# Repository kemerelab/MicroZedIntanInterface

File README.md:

# MicroZedIntanInterface

An FPGA data-acquisition interface for **Intan RHD2000-style neural recording chips**, built
on a **MicroZed** (Xilinx Zynq-7020) with a custom carrier PCB. The PL talks to up to two
cables of RHD2000 chips over a DDR SPI protocol; the PS streams the data over the network.

- Up to **256 channels @ 30 ksps** (two cables × 128 ch, Intan-standard 12-pin Omnetics, single + DDR).
- A user-programmable per-cable phase delay compensates for cable length.
- **TCP control** (port 0x6900 / 26880) + **UDP data stream** (port 0x6800 / 26624, ~9 MB/s per cable, ~18 MB/s at full config).
- Data path: `Intan ──SPI(DDR)──► PL ──BRAM──► (AXI CDMA) ──► PS ──UDP──► host`.

MicroZed SOMs are ~$300 (e.g. [Newark](https://www.newark.com/avnet/aes-z7mb-7z020-som-i-g-rev-h/eval-brd-32bit-fpga-arm-cortex/dp/62AJ7410)).
The [carrier PCB](pcb/KiCad-Project/) is manufactured at JLCPCB.

## Documentation

- **[Getting up and running](docs/getting-started.md)** — assembling the board (Omnetics
  epoxy), the MicroZed boot jumpers, copying the boot image to SD, and building from source.
- **[Command & packet structure](docs/protocol.md)** — the TCP command set, the UDP packet
  format, and the register map.
- **[CLAUDE.md](CLAUDE.md)** — architecture, build commands, and conventions for developers.
- **[ROADMAP.md](ROADMAP.md)** — status and planned work. **[overview.txt](overview.txt)** —
  the deeper architectural narrative.

## Host software

The board's protocol has two reference clients (both speak TCP control + UDP capture):

- **`remote/net.py`** — a single-file Python client for bring-up, cable/phase auto-detection,
  and testing. The human-readable reference for the command set and packet format.
- **[ephys-socket](https://github.com/ckemere/ephys-socket)** — the OpenEphys GUI plugin for
  real recording and visualization (neural + aux/accelerometer channels, fast settle, banked
  aux commands).

The firmware (`firmware/`), `remote/net.py`, and the plugin are the **three consumers of the
same register/packet contract** — keep them in sync when changing the protocol.

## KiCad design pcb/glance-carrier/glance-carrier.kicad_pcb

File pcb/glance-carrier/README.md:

# KiCad design files and production files

The PCB design was dervied from work by Viktor Nokolov licensed under the Creative Commons Zero license. His original project can be found here [https://github.com/viktor-nikolov/MicroZed-carrier-board](https://github.com/viktor-nikolov/MicroZed-carrier-board).

### Revision 1.0 Notes
Board revision 1.0 fixes the bug in 0.11, and transitions from 2 layer to 4 layer fabrication. This allows for
a smaller and slightly more case-friendly layout (digital IO on the same side of the PCB as Intan/Omnetics 
connectors, and USB-C power moved to the same side as the ethernet connector).

### Revision 0.11 Notes
Board revision 0.11 was used for initial testing. There was an error in the connectivity for the USB-UART
bridge. We fixed this with a bodge that is circled in the image below.

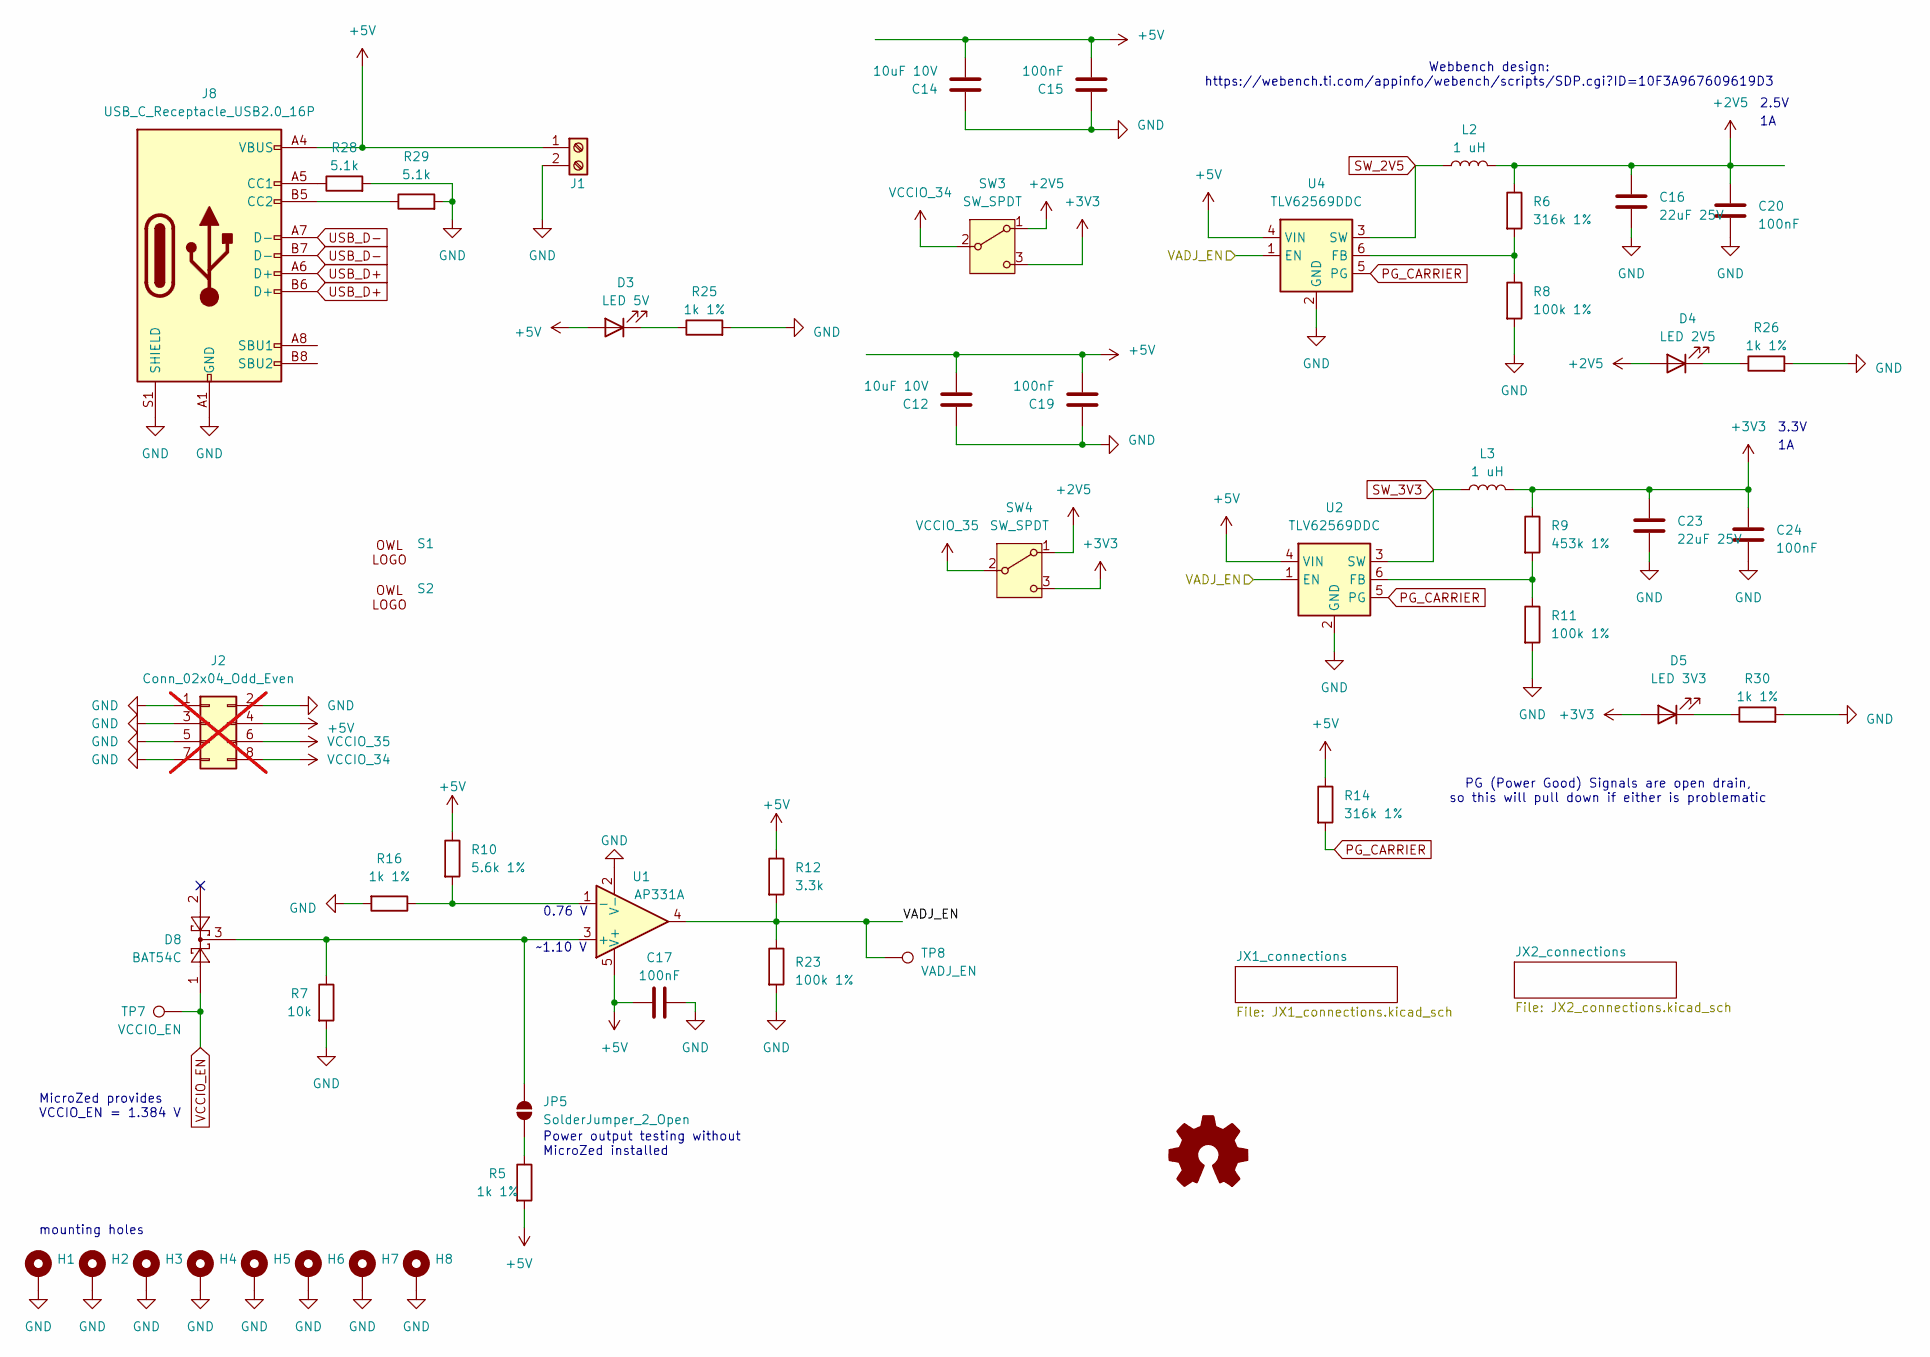
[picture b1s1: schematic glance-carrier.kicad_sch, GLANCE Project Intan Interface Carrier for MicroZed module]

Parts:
C12, C14: 10uF 10V; C_0603_1608Metric; LCSC C19702
C15, C17, C19, C20, C24: 100nF; C_0402_1005Metric; LCSC C307331
C16, C23: 22uF 25V; C_1206_3216Metric; LCSC C12891
D3: LED 5V; LED_0603_1608Metric; LCSC C2286
D4: LED 2V5; LED_0603_1608Metric; LCSC C2286
D5: LED 3V3; LED_0603_1608Metric; LCSC C2286
D8: BAT54C; SOT-23; LCSC C37704
H1, H2, H3, H4, H5, H6, H7, H8: MountingHole_3.2mm_M3_Pad
J1: Screw_Terminal_01x02; TerminalBlock_TE_282834-2_1x02_P2.54mm_Horizontal
J2: Conn_02x04_Odd_Even; PinSocket_2x04_P2.54mm_Vertical; not fitted
J8: USB_C_Receptacle_USB2.0_16P; USB_C_Receptacle_GCT_USB4105-xx-A_16P_TopMnt_Horizontal; LCSC C5184243
JP5: SolderJumper_2_Open; SolderJumper-2_P1.3mm_Open_RoundedPad1.0x1.5mm
L2, L3: 1 uH; L_1210_3225Metric; LCSC C47492669
R5, R16, R25, R26, R30: 1k 1%; R_0402_1005Metric; LCSC C11702
R6, R14: 316k 1%; R_0402_1005Metric; LCSC C4338094
R7: 10k; R_0402_1005Metric; LCSC C25744
R8, R11, R23: 100k 1%; R_0402_1005Metric; LCSC C25741
R9: 453k 1%; R_0402_1005Metric; LCSC C3025678
R10: 5.6k 1%; R_0402_1005Metric; LCSC C25908
R12: 3.3k; R_0402_1005Metric; LCSC C25890
R28, R29: 5.1k; R_0402_1005Metric; LCSC C25905
S1, S2: RICE_OWL_LOGO; not fitted
SW3, SW4: SW_SPDT; SW_SPDT_PCM12; LCSC C221841
TP7: VCCIO_EN; TestPoint_THTPad_D2.0mm_Drill1.0mm
TP8: VADJ_EN; TestPoint_THTPad_D2.0mm_Drill1.0mm
U1: AP331A; SOT-25-5_L3.0-W1.8-P0.95-LS3.0-BR; LCSC C151034
U2, U4: TLV62569DDC; SOT-23-6; LCSC C398365

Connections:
+2V5: C16.2, C20.1, D4.2 (A), L2.2, R6.1, SW3.1 (A), SW4.1 (A)
+3V3: C23.2, C24.1, D5.2 (A), L3.2, R9.1, SW3.3 (C), SW4.3 (C); also elsewhere on the board
+5V: C12.1, C14.1, C15.2, C17.1, C19.2, D3.2 (A), J1.1, J2.4, J8.A4 (VBUS), J8.A9 (VBUS), J8.B4 (VBUS), J8.B9 (VBUS), R5.2, R10.1, R12.1, R14.1, U1.5 (V+), U2.4 (VIN), U4.4 (VIN); also elsewhere on the board
/VADJ_EN: R12.2, R23.1, TP8.1, U1.4, U2.1 (EN), U4.1 (EN)
GND: C12.2, C14.2, C15.1, C16.1, C17.2, C19.1, C20.2, C23.1, C24.2, H1.1, H2.1, H3.1, H4.1, H5.1, H6.1, H7.1, H8.1, J1.2, J2.1, J2.2, J2.3, J2.5, J2.7, J8.A1 (GND), J8.A12 (GND), J8.B1 (GND), J8.B12 (GND), J8.S1 (SHIELD), R7.2, R8.2, R11.2, R16.2, R23.2, R25.2, R26.2, R28.2, R29.2, R30.2, U1.2 (V-), U2.2 (GND), U4.2 (GND); also elsewhere on the board
unnamed: D3.1 (K), R25.1
unnamed: D4.1 (K), R26.1
unnamed: D5.1 (K), R30.1
unnamed: J8.A5 (CC1), R28.1
unnamed: J8.B5 (CC2), R29.1
unnamed: D8.3, JP5.1 (A), R7.1, U1.3 (+)
unnamed: JP5.2 (B), R5.1
unnamed: R10.2, R16.1, U1.1 (-)
unnamed: R9.2, R11.1, U2.6 (FB)
unnamed: R6.2, R8.1, U4.6 (FB)
PG_CARRIER: R14.2, U2.5 (PG), U4.5 (PG); also elsewhere on the board
SW_2V5: L2.1, U4.3 (SW)
SW_3V3: L3.1, U2.3 (SW)
USB_D+: J8.A6 (D+), J8.B6 (D+); also elsewhere on the board
USB_D-: J8.A7 (D-), J8.B7 (D-); also elsewhere on the board
VCCIO_34: J2.8, SW3.2 (B); also elsewhere on the board
VCCIO_35: J2.6, SW4.2 (B); also elsewhere on the board
VCCIO_EN: D8.1, TP7.1; also elsewhere on the board

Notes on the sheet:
3.3V
mounting holes
2.5V
0.76 V
Webbench design: https://webench.ti.com/appinfo/webench/scripts/SDP.cgi?ID=10F3A967609619D3
~1.10 V
Power output testing without MicroZed installed
MicroZed provides VCCIO_EN = 1.384 V
PG (Power Good) Signals are open drain, so this will pull down if either is problematic

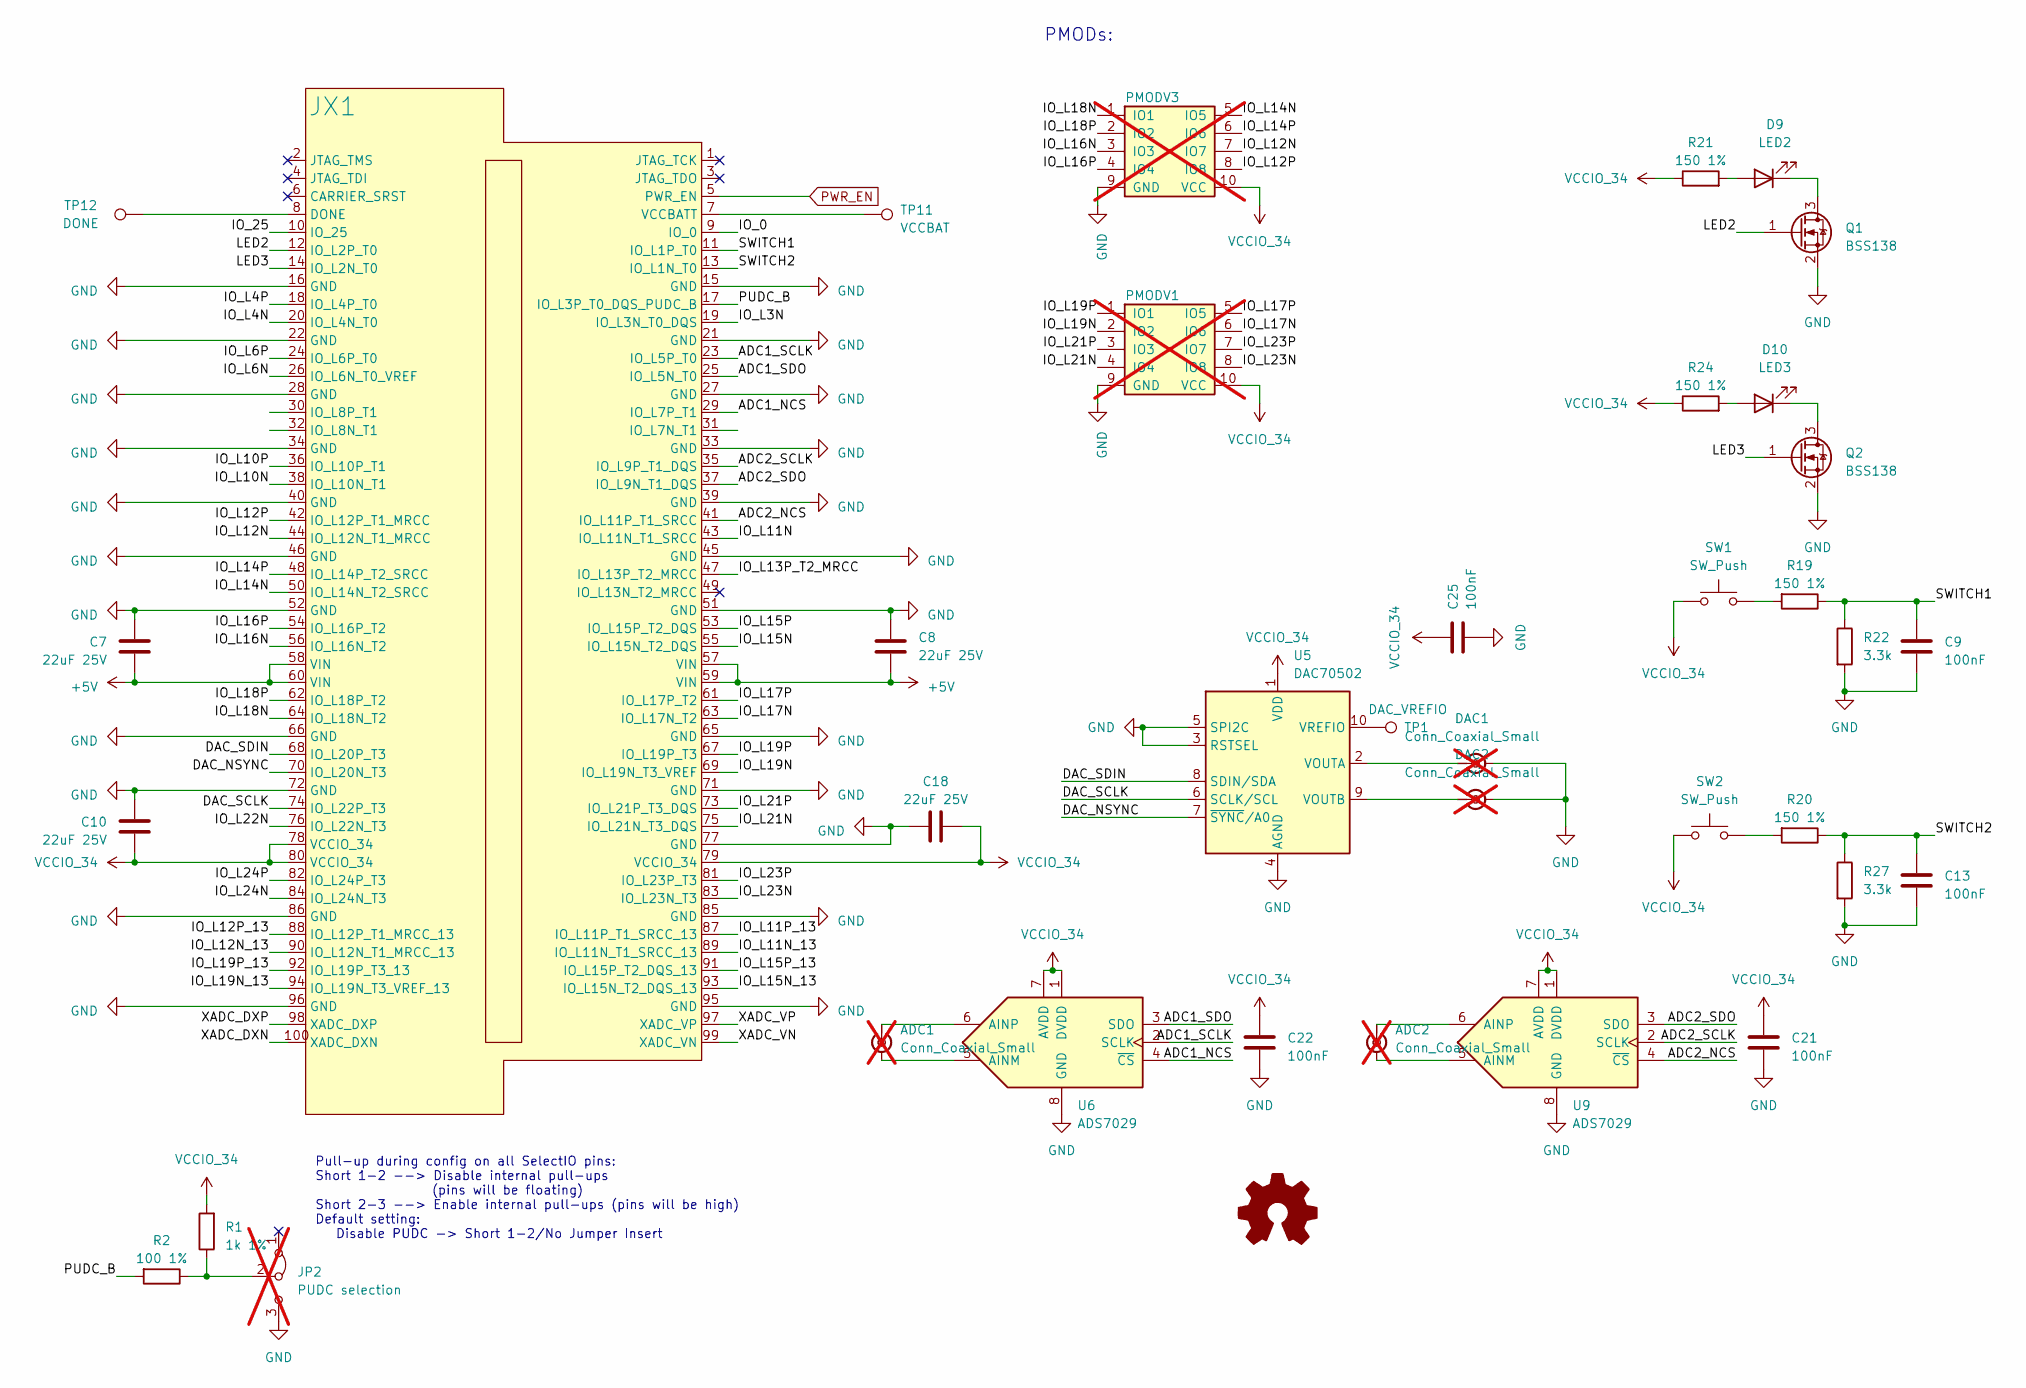
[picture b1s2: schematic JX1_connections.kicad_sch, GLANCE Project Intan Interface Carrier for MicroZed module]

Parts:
ADC1, ADC2: Conn_Coaxial_Small; SMA_Amphenol_901-143_Horizontal; not fitted
C7, C8, C10, C18: 22uF 25V; C_1206_3216Metric; LCSC C12891
C9, C13, C21, C22, C25: 100nF; C_0402_1005Metric; LCSC C307331
D9: LED2; LED_0603_1608Metric; LCSC C2286
D10: LED3; LED_0603_1608Metric; LCSC C2286
DAC1, DAC2: Conn_Coaxial_Small; SMA_Amphenol_901-143_Horizontal; not fitted
JP2: PUDC selection; PinHeader_1x03_P2.54mm_Vertical; not fitted
JX1: BergStak-100pos-plug-61083-101400; LCSC C2764776
PMODV1: PinSocket_2x06_P2.54mm_Vertical; not fitted
PMODV3: PMOD_Socket_Vertical; not fitted
Q1, Q2: BSS138; SOT-23; LCSC C400505
R1: 1k 1%; R_0402_1005Metric; LCSC C11702
R2: 100 1%; R_0402_1005Metric; LCSC C25076
R19, R20, R21, R24: 150 1%; R_0402_1005Metric; LCSC C25082
R22, R27: 3.3k; R_0402_1005Metric; LCSC C25890
SW1, SW2: SW_Push; SW_SPST_TS-1088-xR020; LCSC C720477
TP1: DAC_VREFIO; TestPoint_THTPad_D2.0mm_Drill1.0mm
TP11: VCCBAT; TestPoint_THTPad_D2.0mm_Drill1.0mm
TP12: DONE; TestPoint_THTPad_D2.0mm_Drill1.0mm
U5: DAC70502; Texas_DRX_WSON-10_2.5x2.5mm_P0.5mm; LCSC C880348
U6, U9: ADS7029; VSSOP-8_2.3x2mm_P0.5mm; LCSC C2669867

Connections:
+5V: C7.1, C8.1, JX1.57 (VIN), JX1.58 (VIN), JX1.59 (VIN), JX1.60 (VIN); also elsewhere on the board
/JX1_connections/ADC1_NCS: JX1.29 (IO_L7P_T1), U6.4 (~CS)
/JX1_connections/ADC1_SCLK: JX1.23 (IO_L5P_T0), U6.2 (SCLK)
/JX1_connections/ADC1_SDO: JX1.25 (IO_L5N_T0), U6.3 (SDO)
/JX1_connections/ADC2_NCS: JX1.41 (IO_L11P_T1_SRCC), U9.4 (~CS)
/JX1_connections/ADC2_SCLK: JX1.35 (IO_L9P_T1_DQS), U9.2 (SCLK)
/JX1_connections/ADC2_SDO: JX1.37 (IO_L9N_T1_DQS), U9.3 (SDO)
/JX1_connections/DAC_NSYNC: JX1.70 (IO_L20N_T3), U5.7 (~SYNC/A0)
/JX1_connections/DAC_SCLK: JX1.74 (IO_L22P_T3), U5.6 (SCLK/SCL)
/JX1_connections/DAC_SDIN: JX1.68 (IO_L20P_T3), U5.8 (SDIN/SDA)
/JX1_connections/IO_0: JX1.9 (IO_0)
/JX1_connections/IO_25: JX1.10 (IO_25)
/JX1_connections/IO_L3N: JX1.19 (IO_L3N_T0_DQS)
/JX1_connections/IO_L4N: JX1.20 (IO_L4N_T0)
/JX1_connections/IO_L4P: JX1.18 (IO_L4P_T0)
/JX1_connections/IO_L6N: JX1.26 (IO_L6N_T0_VREF)
/JX1_connections/IO_L6P: JX1.24 (IO_L6P_T0)
/JX1_connections/IO_L10N: JX1.38 (IO_L10N_T1)
/JX1_connections/IO_L10P: JX1.36 (IO_L10P_T1)
/JX1_connections/IO_L11N: JX1.43 (IO_L11N_T1_SRCC)
/JX1_connections/IO_L11N_13: JX1.89 (IO_L11N_T1_SRCC_13)
/JX1_connections/IO_L11P_13: JX1.87 (IO_L11P_T1_SRCC_13)
/JX1_connections/IO_L12N: JX1.44 (IO_L12N_T1_MRCC), PMODV3.7 (IO7)
/JX1_connections/IO_L12N_13: JX1.90 (IO_L12N_T1_MRCC_13)
/JX1_connections/IO_L12P: JX1.42 (IO_L12P_T1_MRCC), PMODV3.8 (IO8)
/JX1_connections/IO_L12P_13: JX1.88 (IO_L12P_T1_MRCC_13)
/JX1_connections/IO_L13P_T2_MRCC: JX1.47 (IO_L13P_T2_MRCC)
/JX1_connections/IO_L14N: JX1.50 (IO_L14N_T2_SRCC), PMODV3.5 (IO5)
/JX1_connections/IO_L14P: JX1.48 (IO_L14P_T2_SRCC), PMODV3.6 (IO6)
/JX1_connections/IO_L15N: JX1.55 (IO_L15N_T2_DQS)
/JX1_connections/IO_L15N_13: JX1.93 (IO_L15N_T2_DQS_13)
/JX1_connections/IO_L15P: JX1.53 (IO_L15P_T2_DQS)
/JX1_connections/IO_L15P_13: JX1.91 (IO_L15P_T2_DQS_13)
/JX1_connections/IO_L16N: JX1.56 (IO_L16N_T2), PMODV3.3 (IO3)
/JX1_connections/IO_L16P: JX1.54 (IO_L16P_T2), PMODV3.4 (IO4)
/JX1_connections/IO_L17N: JX1.63 (IO_L17N_T2), PMODV1.6 (IO6)
/JX1_connections/IO_L17P: JX1.61 (IO_L17P_T2), PMODV1.5 (IO5)
/JX1_connections/IO_L18N: JX1.64 (IO_L18N_T2), PMODV3.1 (IO1)
/JX1_connections/IO_L18P: JX1.62 (IO_L18P_T2), PMODV3.2 (IO2)
/JX1_connections/IO_L19N: JX1.69 (IO_L19N_T3_VREF), PMODV1.2 (IO2)
/JX1_connections/IO_L19N_13: JX1.94 (IO_L19N_T3_VREF_13)
/JX1_connections/IO_L19P: JX1.67 (IO_L19P_T3), PMODV1.1 (IO1)
/JX1_connections/IO_L19P_13: JX1.92 (IO_L19P_T3_13)
/JX1_connections/IO_L21N: JX1.75 (IO_L21N_T3_DQS), PMODV1.4 (IO4)
/JX1_connections/IO_L21P: JX1.73 (IO_L21P_T3_DQS), PMODV1.3 (IO3)
/JX1_connections/IO_L22N: JX1.76 (IO_L22N_T3)
/JX1_connections/IO_L23N: JX1.83 (IO_L23N_T3), PMODV1.8 (IO8)
/JX1_connections/IO_L23P: JX1.81 (IO_L23P_T3), PMODV1.7 (IO7)
/JX1_connections/IO_L24N: JX1.84 (IO_L24N_T3)
/JX1_connections/IO_L24P: JX1.82 (IO_L24P_T3)
/JX1_connections/LED2: JX1.12 (IO_L2P_T0), Q1.1 (G)
/JX1_connections/LED3: JX1.14 (IO_L2N_T0), Q2.1 (G)
/JX1_connections/PUDC_B: JX1.17 (IO_L3P_T0_DQS_PUDC_B), R2.2
/JX1_connections/SWITCH1: C9.1, JX1.11 (IO_L1P_T0), R19.1, R22.1
/JX1_connections/SWITCH2: C13.1, JX1.13 (IO_L1N_T0), R20.1, R27.1
/JX1_connections/XADC_DXN: JX1.100 (XADC_DXN)
/JX1_connections/XADC_DXP: JX1.98 (XADC_DXP)
/JX1_connections/XADC_VN: JX1.99 (XADC_VN)
/JX1_connections/XADC_VP: JX1.97 (XADC_VP)
GND: C7.2, C8.2, C9.2, C10.2, C13.2, C18.2, C21.2, C22.2, C25.2, DAC1.2 (Ext), DAC2.2 (Ext), JP2.3 (B), JX1.15 (GND), JX1.16 (GND), JX1.21 (GND), JX1.22 (GND), JX1.27 (GND), JX1.28 (GND), JX1.33 (GND), JX1.34 (GND), JX1.39 (GND), JX1.40 (GND), JX1.45 (GND), JX1.46 (GND), JX1.51 (GND), JX1.52 (GND), JX1.65 (GND), JX1.66 (GND), JX1.71 (GND), JX1.72 (GND), JX1.77 (GND), JX1.85 (GND), JX1.86 (GND), JX1.95 (GND), JX1.96 (GND), PMODV1.9 (GND), PMODV3.9 (GND), Q1.2 (S), Q2.2 (S), R22.2, R27.2, U5.3 (RSTSEL), U5.4 (AGND), U5.5 (SPI2C), U6.8 (GND), U9.8 (GND); also elsewhere on the board
unnamed: ADC1.2 (Ext), U6.5 (AINM)
unnamed: ADC1.1 (In), U6.6 (AINP)
unnamed: ADC2.2 (Ext), U9.5 (AINM)
unnamed: ADC2.1 (In), U9.6 (AINP)
unnamed: D9.2 (A), R21.2
unnamed: D9.1 (K), Q1.3 (D)
unnamed: D10.2 (A), R24.2
unnamed: D10.1 (K), Q2.3 (D)
unnamed: DAC1.1 (In), U5.2 (VOUTA)
unnamed: DAC2.1 (In), U5.9 (VOUTB)
unnamed: JP2.2 (C), R1.1, R2.1
unnamed: JX1.8 (DONE), TP12.1
unnamed: JX1.7 (VCCBATT), TP11.1
unnamed: R19.2, SW1.2
unnamed: R20.2, SW2.2
unnamed: TP1.1, U5.10 (VREFIO)
PWR_EN: JX1.5 (PWR_EN)
VCCIO_34: C10.1, C18.1, C21.1, C22.1, C25.1, JX1.78 (VCCIO_34), JX1.79 (VCCIO_34), JX1.80 (VCCIO_34), PMODV1.10 (VCC), PMODV3.10 (VCC), R1.2, R21.1, R24.1, SW1.1, SW2.1, U5.1 (VDD), U6.1 (DVDD), U6.7 (AVDD), U9.1 (DVDD), U9.7 (AVDD); also elsewhere on the board

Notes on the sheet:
PMODs:
Pull-up during config on all SelectIO pins: Short 1-2 --> Disable internal pull-ups (pins will be floating) Short 2-3 --> Enable internal pull-ups (pins will be high) Default setting: Disable PUDC -> Short 1-2/No Jumper Insert

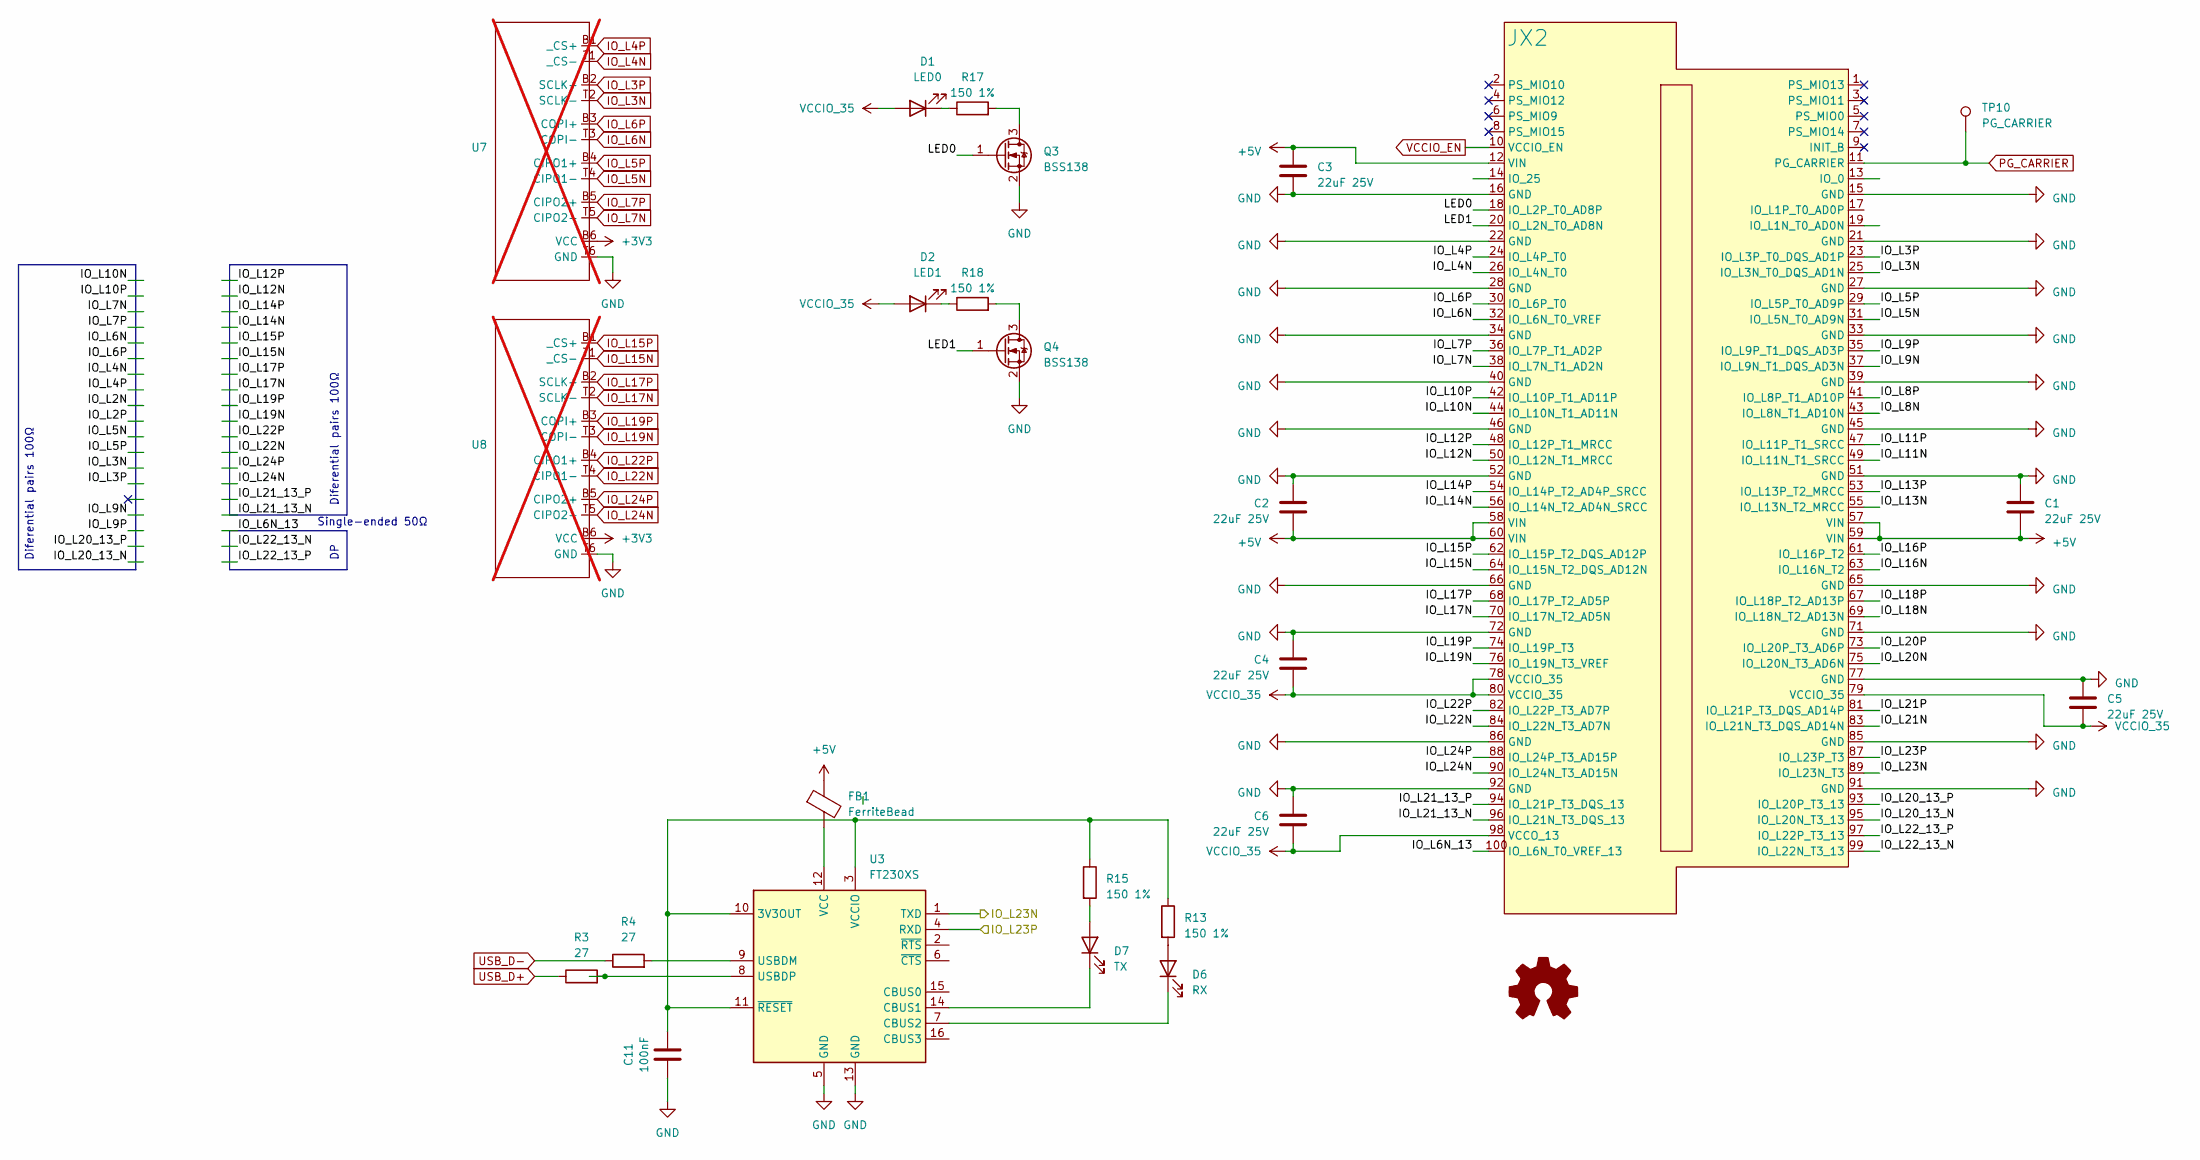
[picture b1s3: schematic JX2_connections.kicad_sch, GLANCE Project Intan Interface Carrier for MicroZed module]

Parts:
C1, C2, C3, C4, C5, C6: 22uF 25V; C_1206_3216Metric; LCSC C12891
C11: 100nF; C_0402_1005Metric; LCSC C307331
D1: LED0; LED_0603_1608Metric; LCSC C2286
D2: LED1; LED_0603_1608Metric; LCSC C2286
D6: RX; LED_0603_1608Metric; LCSC C2286
D7: TX; LED_0603_1608Metric; LCSC C2286
FB1: FerriteBead; L_0805_2012Metric; LCSC C85840
JX2: BergStak-100pos-plug-61083-101400; LCSC C2764776
Q3, Q4: BSS138; SOT-23; LCSC C400505
R3, R4: 27; R_0402_1005Metric; LCSC C413051
R13, R15, R17, R18: 150 1%; R_0402_1005Metric; LCSC C25082
TP10: PG_CARRIER; TestPoint_THTPad_D2.0mm_Drill1.0mm
U3: FT230XS; SSOP-16_3.9x4.9mm_P0.635mm; LCSC C69082
U7, U8: OMNETICS_PZN-12-AA; not fitted

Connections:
+3V3: U7.B6 (VCC), U8.B6 (VCC); also elsewhere on the board
+5V: C1.1, C2.1, C3.1, FB1.1, JX2.12 (VIN), JX2.57 (VIN), JX2.58 (VIN), JX2.59 (VIN), JX2.60 (VIN); also elsewhere on the board
/JX2_connections/IO_L6N_13: JX2.100 (IO_L6N_T0_VREF_13)
/JX2_connections/IO_L8N: JX2.43 (IO_L8N_T1_AD10N)
/JX2_connections/IO_L8P: JX2.41 (IO_L8P_T1_AD10P)
/JX2_connections/IO_L9N: JX2.37 (IO_L9N_T1_DQS_AD3N)
/JX2_connections/IO_L9P: JX2.35 (IO_L9P_T1_DQS_AD3P)
/JX2_connections/IO_L10N: JX2.44 (IO_L10N_T1_AD11N)
/JX2_connections/IO_L10P: JX2.42 (IO_L10P_T1_AD11P)
/JX2_connections/IO_L11N: JX2.49 (IO_L11N_T1_SRCC)
/JX2_connections/IO_L11P: JX2.47 (IO_L11P_T1_SRCC)
/JX2_connections/IO_L12N: JX2.50 (IO_L12N_T1_MRCC)
/JX2_connections/IO_L12P: JX2.48 (IO_L12P_T1_MRCC)
/JX2_connections/IO_L13N: JX2.55 (IO_L13N_T2_MRCC)
/JX2_connections/IO_L13P: JX2.53 (IO_L13P_T2_MRCC)
/JX2_connections/IO_L14N: JX2.56 (IO_L14N_T2_AD4N_SRCC)
/JX2_connections/IO_L14P: JX2.54 (IO_L14P_T2_AD4P_SRCC)
/JX2_connections/IO_L16N: JX2.63 (IO_L16N_T2)
/JX2_connections/IO_L16P: JX2.61 (IO_L16P_T2)
/JX2_connections/IO_L18N: JX2.69 (IO_L18N_T2_AD13N)
/JX2_connections/IO_L18P: JX2.67 (IO_L18P_T2_AD13P)
/JX2_connections/IO_L20N: JX2.75 (IO_L20N_T3_AD6N)
/JX2_connections/IO_L20P: JX2.73 (IO_L20P_T3_AD6P)
/JX2_connections/IO_L20_13_N: JX2.95 (IO_L20N_T3_13)
/JX2_connections/IO_L20_13_P: JX2.93 (IO_L20P_T3_13)
/JX2_connections/IO_L21N: JX2.83 (IO_L21N_T3_DQS_AD14N)
/JX2_connections/IO_L21P: JX2.81 (IO_L21P_T3_DQS_AD14P)
/JX2_connections/IO_L21_13_N: JX2.96 (IO_L21N_T3_DQS_13)
/JX2_connections/IO_L21_13_P: JX2.94 (IO_L21P_T3_DQS_13)
/JX2_connections/IO_L22_13_N: JX2.99 (IO_L22N_T3_13)
/JX2_connections/IO_L22_13_P: JX2.97 (IO_L22P_T3_13)
/JX2_connections/IO_L23N: JX2.89 (IO_L23N_T3), U3.1 (TXD)
/JX2_connections/IO_L23P: JX2.87 (IO_L23P_T3), U3.4 (RXD)
/JX2_connections/LED0: JX2.18 (IO_L2P_T0_AD8P), Q3.1 (G)
/JX2_connections/LED1: JX2.20 (IO_L2N_T0_AD8N), Q4.1 (G)
GND: C1.2, C2.2, C3.2, C4.2, C5.1, C6.2, C11.2, JX2.15 (GND), JX2.16 (GND), JX2.21 (GND), JX2.22 (GND), JX2.27 (GND), JX2.28 (GND), JX2.33 (GND), JX2.34 (GND), JX2.39 (GND), JX2.40 (GND), JX2.45 (GND), JX2.46 (GND), JX2.51 (GND), JX2.52 (GND), JX2.65 (GND), JX2.66 (GND), JX2.71 (GND), JX2.72 (GND), JX2.77 (GND), JX2.85 (GND), JX2.86 (GND), JX2.91 (GND), JX2.92 (GND), Q3.2 (S), Q4.2 (S), U3.5 (GND), U3.13 (GND), U7.T6 (GND), U8.T6 (GND); also elsewhere on the board
IO_L3N: JX2.25 (IO_L3N_T0_DQS_AD1N), U7.T2 (SCLK-)
IO_L3P: JX2.23 (IO_L3P_T0_DQS_AD1P), U7.B2 (SCLK+)
IO_L4N: JX2.26 (IO_L4N_T0), U7.T1 (_CS-)
IO_L4P: JX2.24 (IO_L4P_T0), U7.B1 (_CS+)
IO_L5N: JX2.31 (IO_L5N_T0_AD9N), U7.T4 (CIPO1-)
IO_L5P: JX2.29 (IO_L5P_T0_AD9P), U7.B4 (CIPO1+)
IO_L6N: JX2.32 (IO_L6N_T0_VREF), U7.T3 (COPI-)
IO_L6P: JX2.30 (IO_L6P_T0), U7.B3 (COPI+)
IO_L7N: JX2.38 (IO_L7N_T1_AD2N), U7.T5 (CIPO2-)
IO_L7P: JX2.36 (IO_L7P_T1_AD2P), U7.B5 (CIPO2+)
IO_L15N: JX2.64 (IO_L15N_T2_DQS_AD12N), U8.T1 (_CS-)
IO_L15P: JX2.62 (IO_L15P_T2_DQS_AD12P), U8.B1 (_CS+)
IO_L17N: JX2.70 (IO_L17N_T2_AD5N), U8.T2 (SCLK-)
IO_L17P: JX2.68 (IO_L17P_T2_AD5P), U8.B2 (SCLK+)
IO_L19N: JX2.76 (IO_L19N_T3_VREF), U8.T3 (COPI-)
IO_L19P: JX2.74 (IO_L19P_T3), U8.B3 (COPI+)
IO_L22N: JX2.84 (IO_L22N_T3_AD7N), U8.T4 (CIPO1-)
IO_L22P: JX2.82 (IO_L22P_T3_AD7P), U8.B4 (CIPO1+)
IO_L24N: JX2.90 (IO_L24N_T3_AD15N), U8.T5 (CIPO2-)
IO_L24P: JX2.88 (IO_L24P_T3_AD15P), U8.B5 (CIPO2+)
unnamed: D1.1 (K), R17.1
unnamed: D2.1 (K), R18.1
unnamed: D6.2 (A), R13.2
unnamed: D6.1 (K), U3.7 (CBUS2)
unnamed: D7.2 (A), R15.2
unnamed: D7.1 (K), U3.14 (CBUS1)
unnamed: Q3.3 (D), R17.2
unnamed: Q4.3 (D), R18.2
unnamed: C11.1, R13.1, R15.1, U3.3 (VCCIO), U3.10 (3V3OUT), U3.11 (~RESET)
unnamed: R4.2, U3.9 (USBDM)
unnamed: R3.2, U3.8 (USBDP)
unnamed: FB1.2, U3.12 (VCC)
PG_CARRIER: JX2.11 (PG_CARRIER), TP10.1; also elsewhere on the board
USB_D+: R3.1; also elsewhere on the board
USB_D-: R4.1; also elsewhere on the board
VCCIO_35: C4.1, C5.2, C6.1, D1.2 (A), D2.2 (A), JX2.78 (VCCIO_35), JX2.79 (VCCIO_35), JX2.80 (VCCIO_35), JX2.98 (VCCO_13); also elsewhere on the board
VCCIO_EN: JX2.10 (VCCIO_EN); also elsewhere on the board

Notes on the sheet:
Single-ended 50Ω
Diferential pairs 100Ω

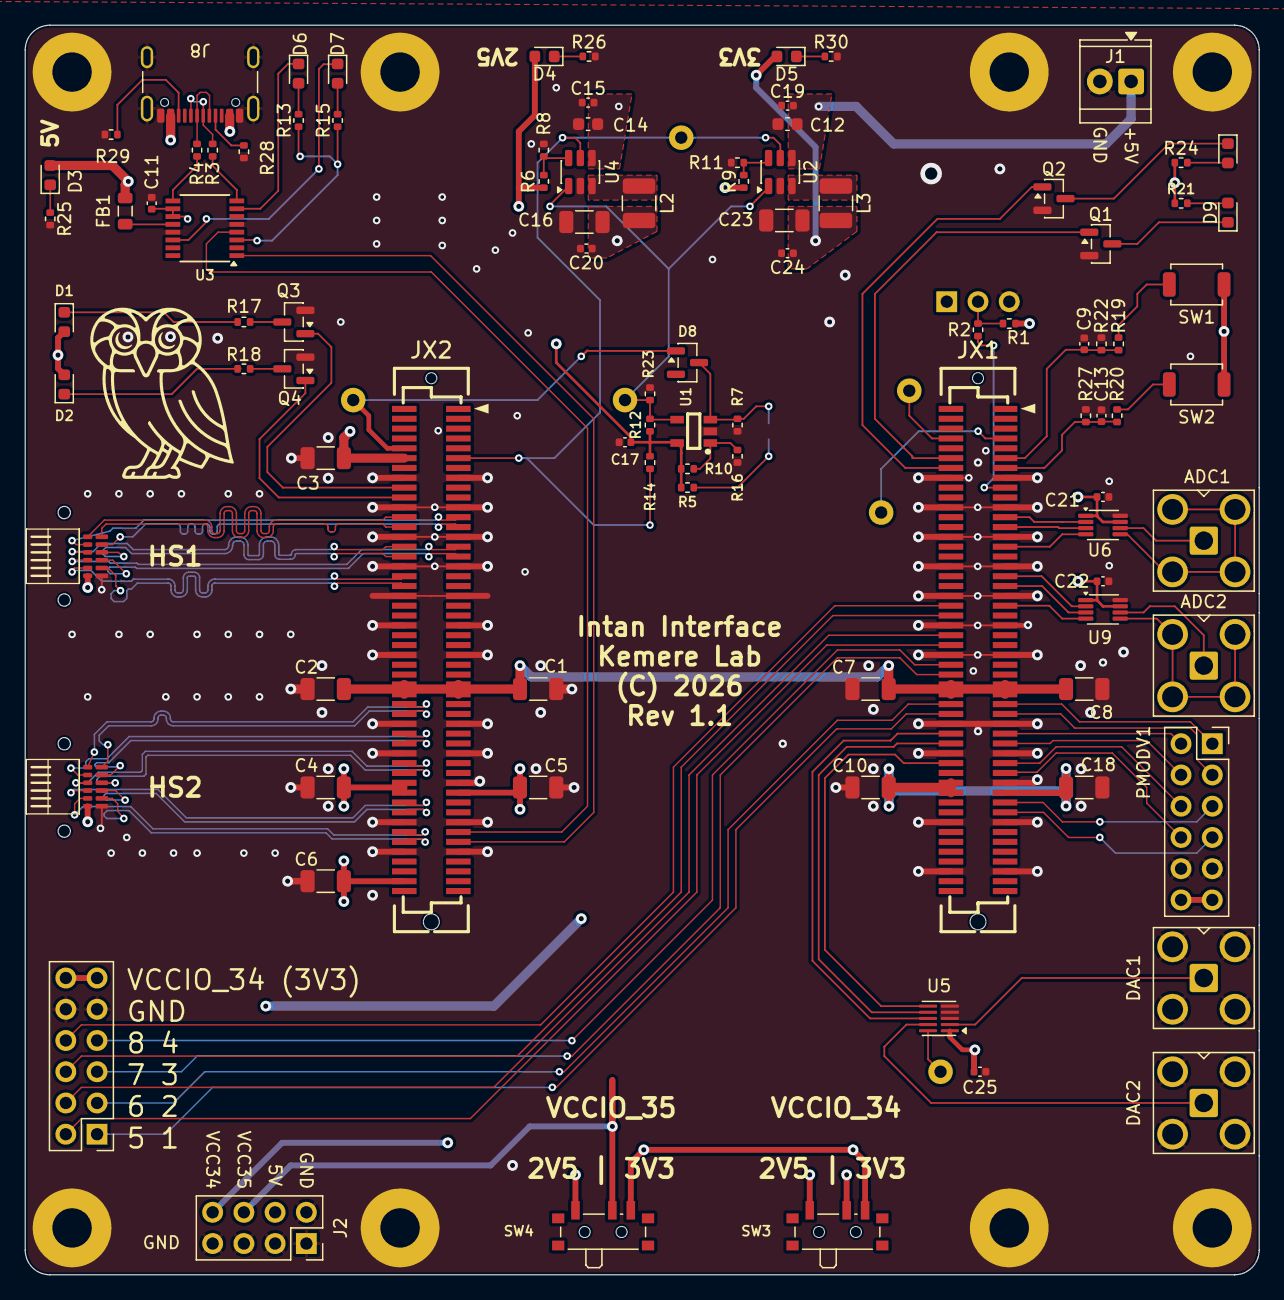
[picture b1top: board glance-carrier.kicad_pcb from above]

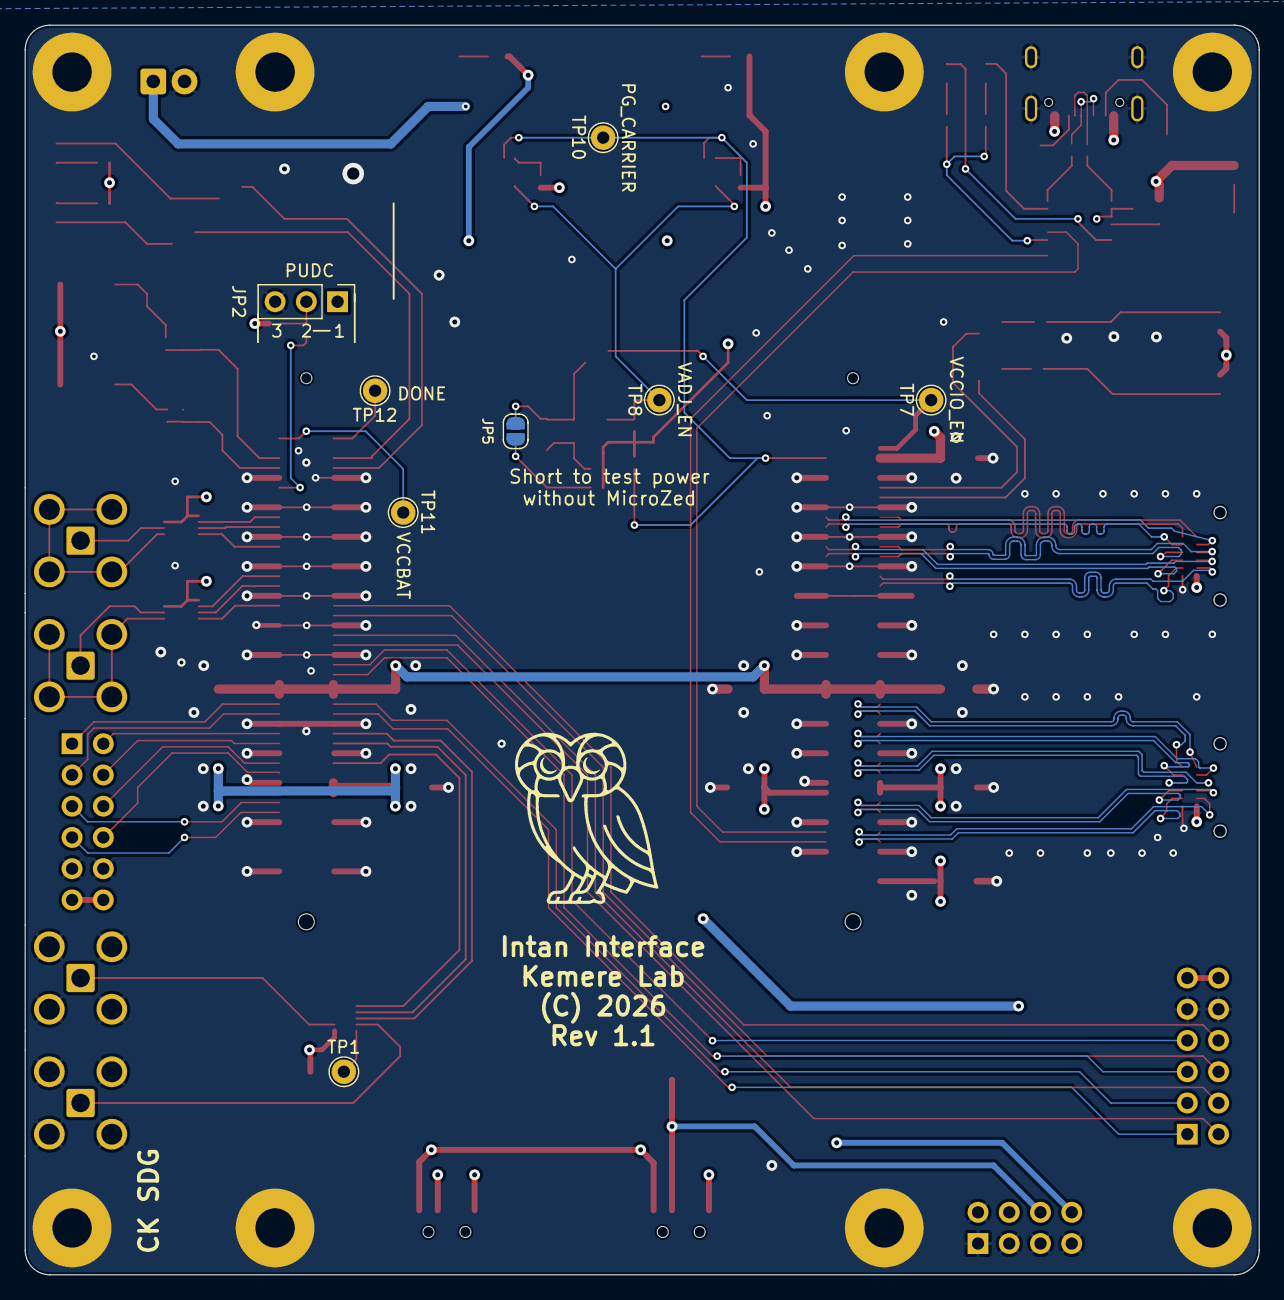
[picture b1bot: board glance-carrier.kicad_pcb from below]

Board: 4 copper layers, 100.3 x 101.6 mm, 114 parts (9 on the bottom side), 105 nets.

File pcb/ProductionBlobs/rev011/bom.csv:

Designator,Footprint,Quantity,Value,LCSC Part #
"C1, C16, C23",1206,3,22uF 10V,C5672
"C10, C18, C2, C3, C4, C5, C6, C7, C8",1206,9,22uF,C5672
"C11, C13, C15, C17, C19, C20, C24, C9",0603,8,100nF,C66501
"C12, C14",0603,2,10uF 10V,C19702
"D1, D2",LED0805,2,LED yellow,C2296
D10,0805,1,LED 4,C2296
D3,0603,1,LED 5V,C2833058
D4,0603,1,LED 2V5,C2833058
D5,0603,1,LED 3V3,C2833058
D6,0603,1,RX,C2833058
D7,0603,1,TX,C2833058
D8,SOT-23,1,BAT54C,C37704
D9,0805,1,LED 3,C2296
FB1,0805,1,FerriteBead,
J2,PinSocket_2x05_P2.54mm_Vertical,1,Conn_02x05_Odd_Even,
J4,USB_C_Receptacle_GCT_USB4105-xx-A_16P_TopMnt_Horizontal,1,USB_C_Receptacle_USB2.0_16P,
"JX1, JX2",BergStak-100pos-plug-61083-101400,2,~,C2764776
"L2, L3",1008,2,1 uH,
"Q1, Q2, Q3, Q4",SOT-23,4,BSS138,C400505
"R1, R5",0603,2,1K,C21190
R10,0603,1,5K6 1%,C22843
"R11, R8",0603,2,100k 1%,
R12,0603,1,3K,C4211
"R13, R15",0603,2,133R,C4326496
"R14, R6",0603,2,316k 1%,
R16,0603,1,1K 1%,C23228
"R17, R18, R21, R24",0603,4,150R,C22808
"R19, R2, R20",0603,3,100R,C22775
"R22, R27",0603,2,3K3,C22978
R23,0603,1,100K,C25803
R25,0603,1,4K87,C2097544
"R26, R30",0603,2,1K54,C100784
"R28, R29",0603,2,5K1,C2097544
"R3, R4",0603,2,27R,C4326496
R7,0603,1,10K,C25804
R9,0603,1,453k 1%,
"SW1, SW2",Switch-TH_4P-L6.0-W6.0-P4.50-LS6.5,2,SW_MEC_5E,C445493
U1,SOT-25-5_L3.0-W1.8-P0.95-LS3.0-BR,1,AP331A,C151034
"U2, U9",SOT-23-6,2,TLV62568DDC,
U3,SSOP-16_3.9x4.9mm_P0.635mm,1,FT230XS,
"U7, U8",OMNETICS_PZN-12-AA,2,~,

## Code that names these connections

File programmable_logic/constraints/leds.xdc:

# SPDX-License-Identifier: MIT
# SPDX-FileCopyrightText: 2025-2026 Caleb Kemere, Reet Sinha, Allen Mikhailov, Rice University

# LED Constraints
# LED0 - Heartbeat (system alive) (connected to JX2 / VCCO bank 35)
set_property PACKAGE_PIN B19 [get_ports led0]
set_property IOSTANDARD LVCMOS25 [get_ports led0]

# LED1 - Transmission active  (connected to JX2 / VCCO bank 35)
set_property PACKAGE_PIN A20 [get_ports led1]
set_property IOSTANDARD LVCMOS25 [get_ports led1]

# LED2 - TBD (connected to JX1 / VCCO bank 34)
set_property PACKAGE_PIN T14 [get_ports led2]
set_property IOSTANDARD LVCMOS25 [get_ports led2]

# LED3 - TBD  (connected to JX1 / VCCO bank 34)
set_property PACKAGE_PIN T15 [get_ports led3]
set_property IOSTANDARD LVCMOS25 [get_ports led3]

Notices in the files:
pcb/KiCad-Project/JX1_connections.kicad_sch:
License: CERN-OHL-P v2
(c) 2023 Viktor Nikolov
pcb/MicroZed-IntanInterface-2Layer/JX1_connections.kicad_sch:
License: Creative Commons Zero
pcb/glance-carrier/glance-carrier.kicad_pcb:
(c) 2026 Caleb Kemere
(C) 2026
pcb/glance-carrier/glance-carrier.kicad_sch:
(c) 2025-2026 Caleb Kemere
